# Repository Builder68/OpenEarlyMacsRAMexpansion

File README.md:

# Open Early Macs RAM Expansion
#
 ## SUMMARY

This upgrade utilizes 1Mb x 16-bit RAM ICs with 1024 refresh cycles, providing up to 4MB of RAM for Macintosh 128K and 512K equipped with the 128KB ROM (Macintosh Plus ROM). 
Testing has confirmed compatibility with a Macintosh 512Ke, including concurrent use with the ROM-INATOR board. Furthermore, installing this memory expansion alongside a SCSI card (like the MacSnap SCSI) enables the 128KB ROM to identify the machine as a Mac Plus.

*Attention: Due to the way the ROM-INATOR board determines the Mac model it's installed on (Mac Plus or Mac 512Ke), its ROM image needs to be [patched](https://68kmla.org/bb/index.php?threads/early-macintosh-home-brew-4mb-memory-upgrade-board-development.47308/post-544271) before installing this RAM expansion board or any other RAM upgrade.*

## PROJECT STATUS

This project is fully functional on a Mac 512Ke. Although it's expected to work on Mac 128K or 512K systems with the 128KB ROM, this specific compatibility hasn't been tested yet.

## KEY FEATURES

* One single detachable RAM board, which taps several signals through bodge wires with JST connectors and either piggyback sockets or pin headers soldered to components on the LB.
* You can disable RAM expansion through DIP switches on the board.
* A solder jumper allows you to select between two memory size configurations: 2MB or 4MB.
* Compatible with FPM or EDO CMOS RAM ICs of 1Mb x 16 bits.
* The PCB dimensions are designed to allow concurrent installation with [Demik's MacSnap SCSI replica board](https://github.com/demik/MacSnap-SCSI//). 
* No extensions or additional software are needed; Mac will automatically recognize all the configured RAM upon startup.
## ASSEMBLY

While the assembly process is straightforward, it can be challenging. Reflow soldering, or using solder paste and a heat gun, is highly recommended for the RAM chips and most SMD components. 

Although this might sound highly obvious, I must say it:

Please be sure to get the right schematics for your LB revision.

## SPECIAL THANKS

This project wouldn't be where it is today without the significant contributions of Golden Potato. His collaboration on developing and testing this design was instrumental. From the beginning, his desire was that this design should be free and open source with both of our names attached to it. 
#
#

### 1. RAM EXPANSION BOARD 
Front

Back

## 2. BOM

#
## 3. BEFORE INSTALLING 

### 3.1 Socket machine headers at RP2 & RP3 

Prior to installing the expansion board, resistor arrays RP2 and RP3 must be removed from the LB and replaced with socket pin machine headers.
#
## 4. INSTALLATION

### 4.1 Pin headers
  
Solder machine pin headers (male to male) onto ICs U12E, U13E, and U4F. Then, the board connects to these pin headers via sockets soldered on the backside of the expansion board.

Optionally, you can instead solder DIP sockets onto U12E, U13E, and U4F (piggybacked) and solder male-to-male pin headers to the expansion board.

## 5. Signals to JST connectors

The following tables shows the signals that are collected via bodged wires from the LB to the JST connectors J11 and J12:

### 5.1 J11

| SIGNAL          | Location       | Pin N° | Comment         |
|:---------------:|:--------------:|:------------:|:---------------:|
| /SNDPG2         |Pin N°5 - U2F   |1             |                 |
| /DMA            |Pin N°15 - U2F  |2             |                 |
| VA6             |Pin N°6 - U2F   |3             |                 |
| VA13            |Pin N°12 - U3G  |4             |                 |
| A18             |Pin N°46 - CPU  |5             |                 |
| VA5             |Pin N°13 - U3G  |6             |                 |

### 5.2 J12

| SIGNAL                | Location on LB   | Pin N° | Comment         |
|:---------------------:|:----------------:|:------------:|:---------------:|
| A17                   |Pin N°45 - CPU    |1             |                 |
| A20                   |Pin N°5 - U4D     |2             |                 |
| A19                   |Pin N°3 - U3D     |3             |                 |
| A21                   |Pin N°50 - CPU    |4             |                 |
| /RAS                  |Left Leg of R4 or Pin N°14 - 4D   |5             |                 | 
| R/WF                  |Right Leg of R33  |6             |                 |
#

## 6. SETTINGS

### 6.1 RAM Expansion Board

#### 6.1.1 IC RAM Type (FPM / EDO)

Solder jumpers JP1 & JP2 selects between FPM or EDO RAM IC types

#### 6.1.2 RAM Size

|JP3              |RAM Size           |
|:---------------:|:-----------------:|
| 2-3             | 2MB               |
| 1-2.            | 4MB.              |

#### 6.1.3 RAM Expansion Enabling (SWB1 & SWB2)

SWB1
|S n°|Expansion RAM Enabled  |  Expansion RAM Disabled |
|:--:|:------------------:|:-------------------:|
| 1  | ON                 |               OFF   |
| 2  | OFF                |               ON    |
| 3  | ON                 |               OFF   |
| 4  | OFF                |               ON    |
| 5  | ON                 |               OFF   |
| 6  | OFF                |               ON    |

SWB2
|S n°|Expansion RAM Enabled  |  Expansion RAM Disabled |
|:--:|:------------------:|:-------------------:|
| 1  | ON                 |               OFF   |
| 2  | OFF                |               ON    |
| 3  | ON                 |               OFF   |
| 4  | OFF                |               ON    |
| 5  | ON                 |               OFF   |
| 6  | ON                 |               OFF   |
| 7  | OFF                |               ON    |
| 8  | OFF                |               ON    |

*Attention: double check all connections and DIP switch settings before power-up*

Good luck. Let us know how it goes here: https://68kmla.org/bb/index.php?threads/early-macintosh-home-brew-4mb-memory-upgrade-board-development.47308/

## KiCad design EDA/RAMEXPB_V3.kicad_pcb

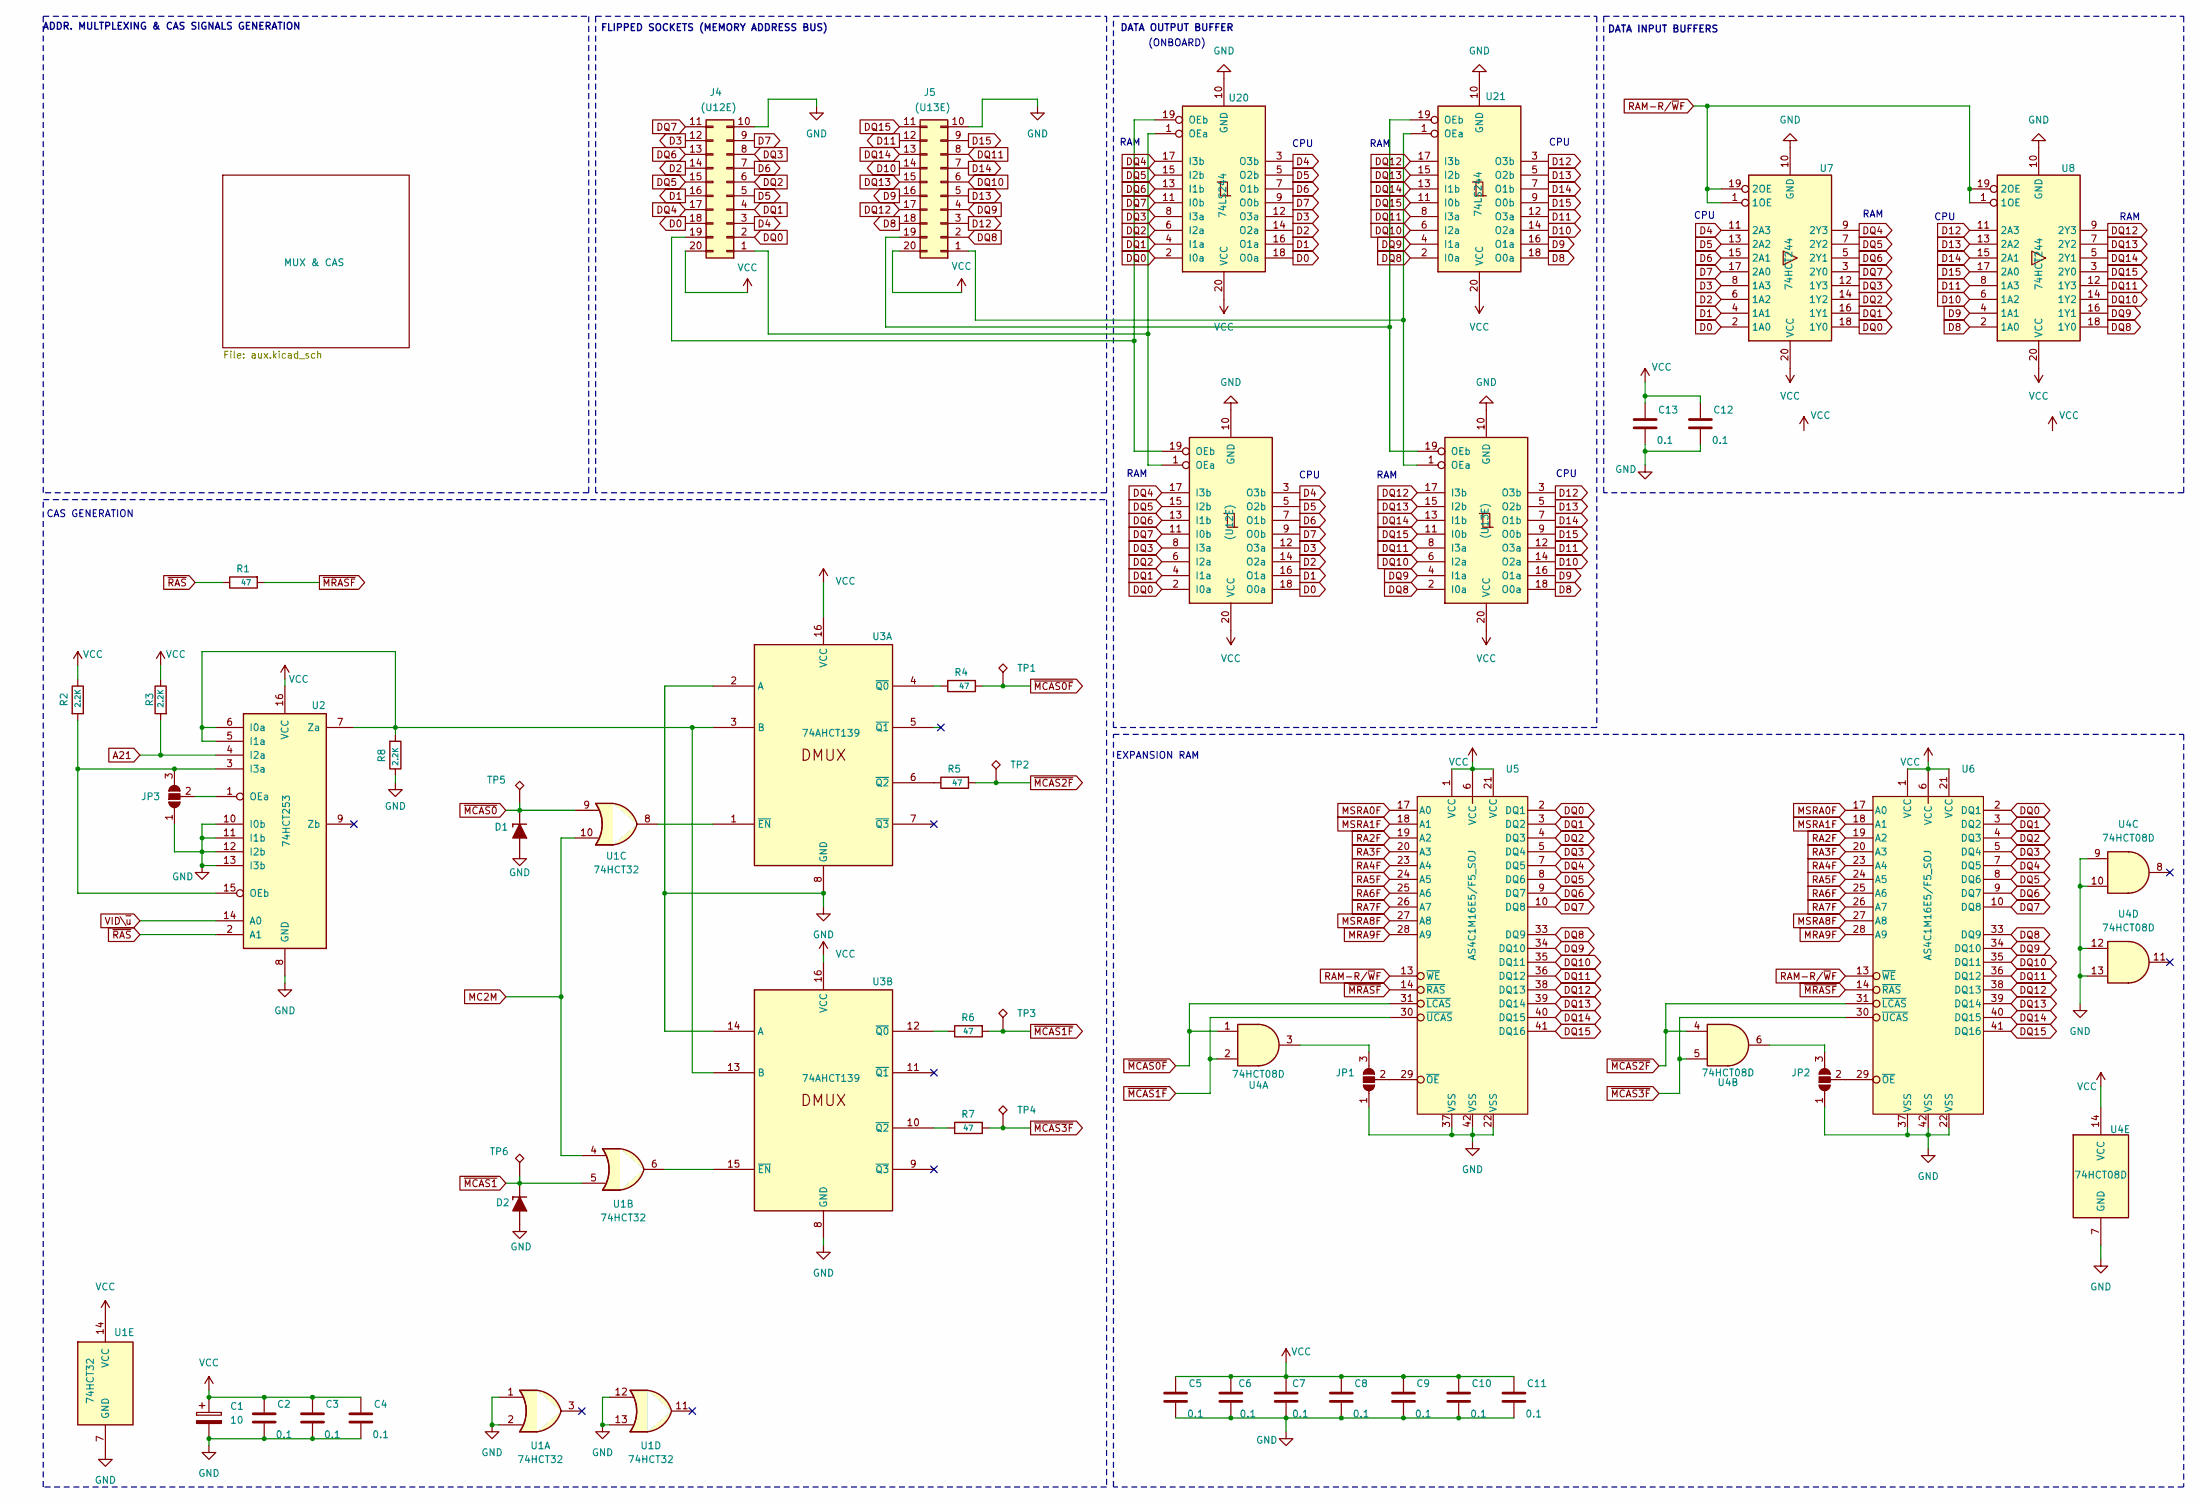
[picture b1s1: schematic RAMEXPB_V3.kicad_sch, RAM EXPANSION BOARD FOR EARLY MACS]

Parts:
C1: 10; CP_EIA-6032-28_Kemet-C_Pad2.25x2.35mm_HandSolder
C2, C3, C4, C5, C6, C7, C8, C9, C10, C11, C12, C13: 0.1; C_0805_2012Metric_Pad1.18x1.45mm_HandSolder
D1, D2: SZMMSZ5V1T1G; D_SOD-123
J4: (U12E); DIP-20_Socket_INV_Flip
J5: (U13E); DIP-20_Socket_INV_Flip
JP1, JP2, JP3: SolderJumper_3_Open; SolderJumper-3_P1.3mm_Open_RoundedPad1.0x1.5mm_NumberLabels
R1, R4, R5, R6, R7: 47; R_0805_2012Metric_Pad1.20x1.40mm_HandSolder
R2, R3, R8: 2.2K; R_0805_2012Metric_Pad1.20x1.40mm_HandSolder
TP1, TP2, TP3, TP4, TP5, TP6: TestPoint_Alt; TestPoint_Pad_D1.0mm
U1: 74HCT32; SO-14_3.9x8.65mm_P1.27mm
U2: 74HCT253; SO-16_3.9x9.9mm_P1.27mm
U3: 74AHCT139; SO-16_3.9x9.9mm_P1.27mm
U4: 74HCT08D; SO-14_3.9x8.65mm_P1.27mm
U5, U6: AS4C1M16E5/F5_SOJ; SOJ-42_400mil
U7, U8: 74HCT244; SOIC-20W_7.5x12.8mm_P1.27mm
U12: (U12E); DIP-20_W7.62mm_Socket
U13: (U13E); DIP-20_W7.62mm_Socket
U20, U21: 74LS244; Socket_DIP-20_7.62mm_Conn_Hole1mm_custom

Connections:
A21: R3.2, U2.4 (I2a); also elsewhere on the board
D0: J4.18, U7.2 (1A0), U12.18 (O0a), U20.18 (O0a)
D1: J4.16, U7.4 (1A1), U12.16 (O1a), U20.16 (O1a)
D2: J4.14, U7.6 (1A2), U12.14 (O2a), U20.14 (O2a)
D3: J4.12, U7.8 (1A3), U12.12 (O3a), U20.12 (O3a)
D4: J4.3, U7.11 (2A3), U12.3 (O3b), U20.3 (O3b)
D5: J4.5, U7.13 (2A2), U12.5 (O2b), U20.5 (O2b)
D6: J4.7, U7.15 (2A1), U12.7 (O1b), U20.7 (O1b)
D7: J4.9, U7.17 (2A0), U12.9 (O0b), U20.9 (O0b)
D8: J5.18, U8.2 (1A0), U13.18 (O0a), U21.18 (O0a)
D9: J5.16, U8.4 (1A1), U13.16 (O1a), U21.16 (O1a)
D10: J5.14, U8.6 (1A2), U13.14 (O2a), U21.14 (O2a)
D11: J5.12, U8.8 (1A3), U13.12 (O3a), U21.12 (O3a)
D12: J5.3, U8.11 (2A3), U13.3 (O3b), U21.3 (O3b)
D13: J5.5, U8.13 (2A2), U13.5 (O2b), U21.5 (O2b)
D14: J5.7, U8.15 (2A1), U13.7 (O1b), U21.7 (O1b)
D15: J5.9, U8.17 (2A0), U13.9 (O0b), U21.9 (O0b)
DQ0: J4.2, U5.2 (DQ1), U6.2 (DQ1), U7.18 (1Y0), U12.2 (I0a), U20.2 (I0a)
DQ1: J4.4, U5.3 (DQ2), U6.3 (DQ2), U7.16 (1Y1), U12.4 (I1a), U20.4 (I1a)
DQ2: J4.6, U5.4 (DQ3), U6.4 (DQ3), U7.14 (1Y2), U12.6 (I2a), U20.6 (I2a)
DQ3: J4.8, U5.5 (DQ4), U6.5 (DQ4), U7.12 (1Y3), U12.8 (I3a), U20.8 (I3a)
DQ4: J4.17, U5.7 (DQ5), U6.7 (DQ5), U7.9 (2Y3), U12.17 (I3b), U20.17 (I3b)
DQ5: J4.15, U5.8 (DQ6), U6.8 (DQ6), U7.7 (2Y2), U12.15 (I2b), U20.15 (I2b)
DQ6: J4.13, U5.9 (DQ7), U6.9 (DQ7), U7.5 (2Y1), U12.13 (I1b), U20.13 (I1b)
DQ7: J4.11, U5.10 (DQ8), U6.10 (DQ8), U7.3 (2Y0), U12.11 (I0b), U20.11 (I0b)
DQ8: J5.2, U5.33 (DQ9), U6.33 (DQ9), U8.18 (1Y0), U13.2 (I0a), U21.2 (I0a)
DQ9: J5.4, U5.34 (DQ10), U6.34 (DQ10), U8.16 (1Y1), U13.4 (I1a), U21.4 (I1a)
DQ10: J5.6, U5.35 (DQ11), U6.35 (DQ11), U8.14 (1Y2), U13.6 (I2a), U21.6 (I2a)
DQ11: J5.8, U5.36 (DQ12), U6.36 (DQ12), U8.12 (1Y3), U13.8 (I3a), U21.8 (I3a)
DQ12: J5.17, U5.38 (DQ13), U6.38 (DQ13), U8.9 (2Y3), U13.17 (I3b), U21.17 (I3b)
DQ13: J5.15, U5.39 (DQ14), U6.39 (DQ14), U8.7 (2Y2), U13.15 (I2b), U21.15 (I2b)
DQ14: J5.13, U5.40 (DQ15), U6.40 (DQ15), U8.5 (2Y1), U13.13 (I1b), U21.13 (I1b)
DQ15: J5.11, U5.41 (DQ16), U6.41 (DQ16), U8.3 (2Y0), U13.11 (I0b), U21.11 (I0b)
GND: C1.2, C2.2, C3.2, C4.2, C5.2, C6.2, C7.2, C8.2, C9.2, C10.2, C11.2, C12.2, C13.2, D1.2 (A), D2.2 (A), J4.10, J5.10, JP1.1 (A), JP2.1 (A), JP3.1 (A), R8.1, U1.1, U1.2, U1.7 (GND), U1.12, U1.13, U2.8 (GND), U2.10 (I0b), U2.11 (I1b), U2.12 (I2b), U2.13 (I3b), U3.2 (A), U3.8 (GND), U3.14 (A), U4.7 (GND), U4.9, U4.10, U4.12, U4.13, U5.22 (VSS), U5.37 (VSS), U5.42 (VSS), U6.22 (VSS), U6.37 (VSS), U6.42 (VSS), U7.10 (GND), U8.10 (GND), U12.10 (GND), U13.10 (GND), U20.10 (GND), U21.10 (GND); also elsewhere on the board
MC2M: U1.4, U1.10; also elsewhere on the board
MRA9F: U5.28 (A9), U6.28 (A9); also elsewhere on the board
MSRA0F: U5.17 (A0), U6.17 (A0); also elsewhere on the board
MSRA1F: U5.18 (A1), U6.18 (A1); also elsewhere on the board
MSRA8F: U5.27 (A8), U6.27 (A8); also elsewhere on the board
unnamed: J4.1, U12.1 (OEa), U20.1 (OEa)
unnamed: J4.19, U12.19 (OEb), U20.19 (OEb)
unnamed: J5.1, U13.1 (OEa), U21.1 (OEa)
unnamed: J5.19, U13.19 (OEb), U21.19 (OEb)
unnamed: JP1.3 (B), U4.3
unnamed: JP1.2 (C), U5.29 (~OE)
unnamed: JP2.3 (B), U4.6
unnamed: JP2.2 (C), U6.29 (~OE)
unnamed: JP3.3 (B), R2.2, U2.3 (I3a), U2.15 (OEb)
unnamed: JP3.2 (C), U2.1 (OEa)
unnamed: R8.2, U2.5 (I1a), U2.6 (I0a), U2.7 (Za), U3.3 (B), U3.13 (B)
unnamed: U1.8, U3.1 (~EN)
unnamed: R4.1, U3.4 (~Q0)
unnamed: R5.1, U3.6 (~Q2)
unnamed: U1.6, U3.15 (~EN)
unnamed: R6.1, U3.12 (~Q0)
unnamed: R7.1, U3.10 (~Q2)
RA2F: U5.19 (A2), U6.19 (A2); also elsewhere on the board
RA3F: U5.20 (A3), U6.20 (A3); also elsewhere on the board
RA4F: U5.23 (A4), U6.23 (A4); also elsewhere on the board
RA5F: U5.24 (A5), U6.24 (A5); also elsewhere on the board
RA6F: U5.25 (A6), U6.25 (A6); also elsewhere on the board
RA7F: U5.26 (A7), U6.26 (A7); also elsewhere on the board
RAM-R/~WF: U5.13 (~WE), U6.13 (~WE), U7.1 (1OE), U7.19 (2OE), U8.1 (1OE), U8.19 (2OE); also elsewhere on the board
VCC: C1.1, C2.1, C3.1, C4.1, C5.1, C6.1, C7.1, C8.1, C9.1, C10.1, C11.1, C12.1, C13.1, J4.20, J5.20, R2.1, R3.1, U1.14 (VCC), U2.16 (VCC), U3.16 (VCC), U4.14 (VCC), U5.1 (VCC), U5.6 (VCC), U5.21 (VCC), U6.1 (VCC), U6.6 (VCC), U6.21 (VCC), U7.20 (VCC), U8.20 (VCC), U12.20 (VCC), U13.20 (VCC), U20.20 (VCC), U21.20 (VCC); also elsewhere on the board
VID\~u: U2.14 (A0); also elsewhere on the board
~MCAS0F: R4.2, TP1.1, U4.1, U5.31 (~LCAS)
~MCAS0: D1.1 (K), TP5.1, U1.9; also elsewhere on the board
~MCAS1F: R6.2, TP3.1, U4.2, U5.30 (~UCAS)
~MCAS1: D2.1 (K), TP6.1, U1.5; also elsewhere on the board
~MCAS2F: R5.2, TP2.1, U4.4, U6.31 (~LCAS)
~MCAS3F: R7.2, TP4.1, U4.5, U6.30 (~UCAS)
~MRASF: R1.2, U5.14 (~RAS), U6.14 (~RAS)
~RAS: R1.1, U2.2 (A1); also elsewhere on the board

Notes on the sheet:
RAM
CPU
DATA INPUT BUFFERS
EXPANSION RAM
DATA OUTPUT BUFFER
CAS GENERATION
FLIPPED SOCKETS (MEMORY ADDRESS BUS)
(ONBOARD)
ADDR. MULTPLEXING & CAS SIGNALS GENERATION

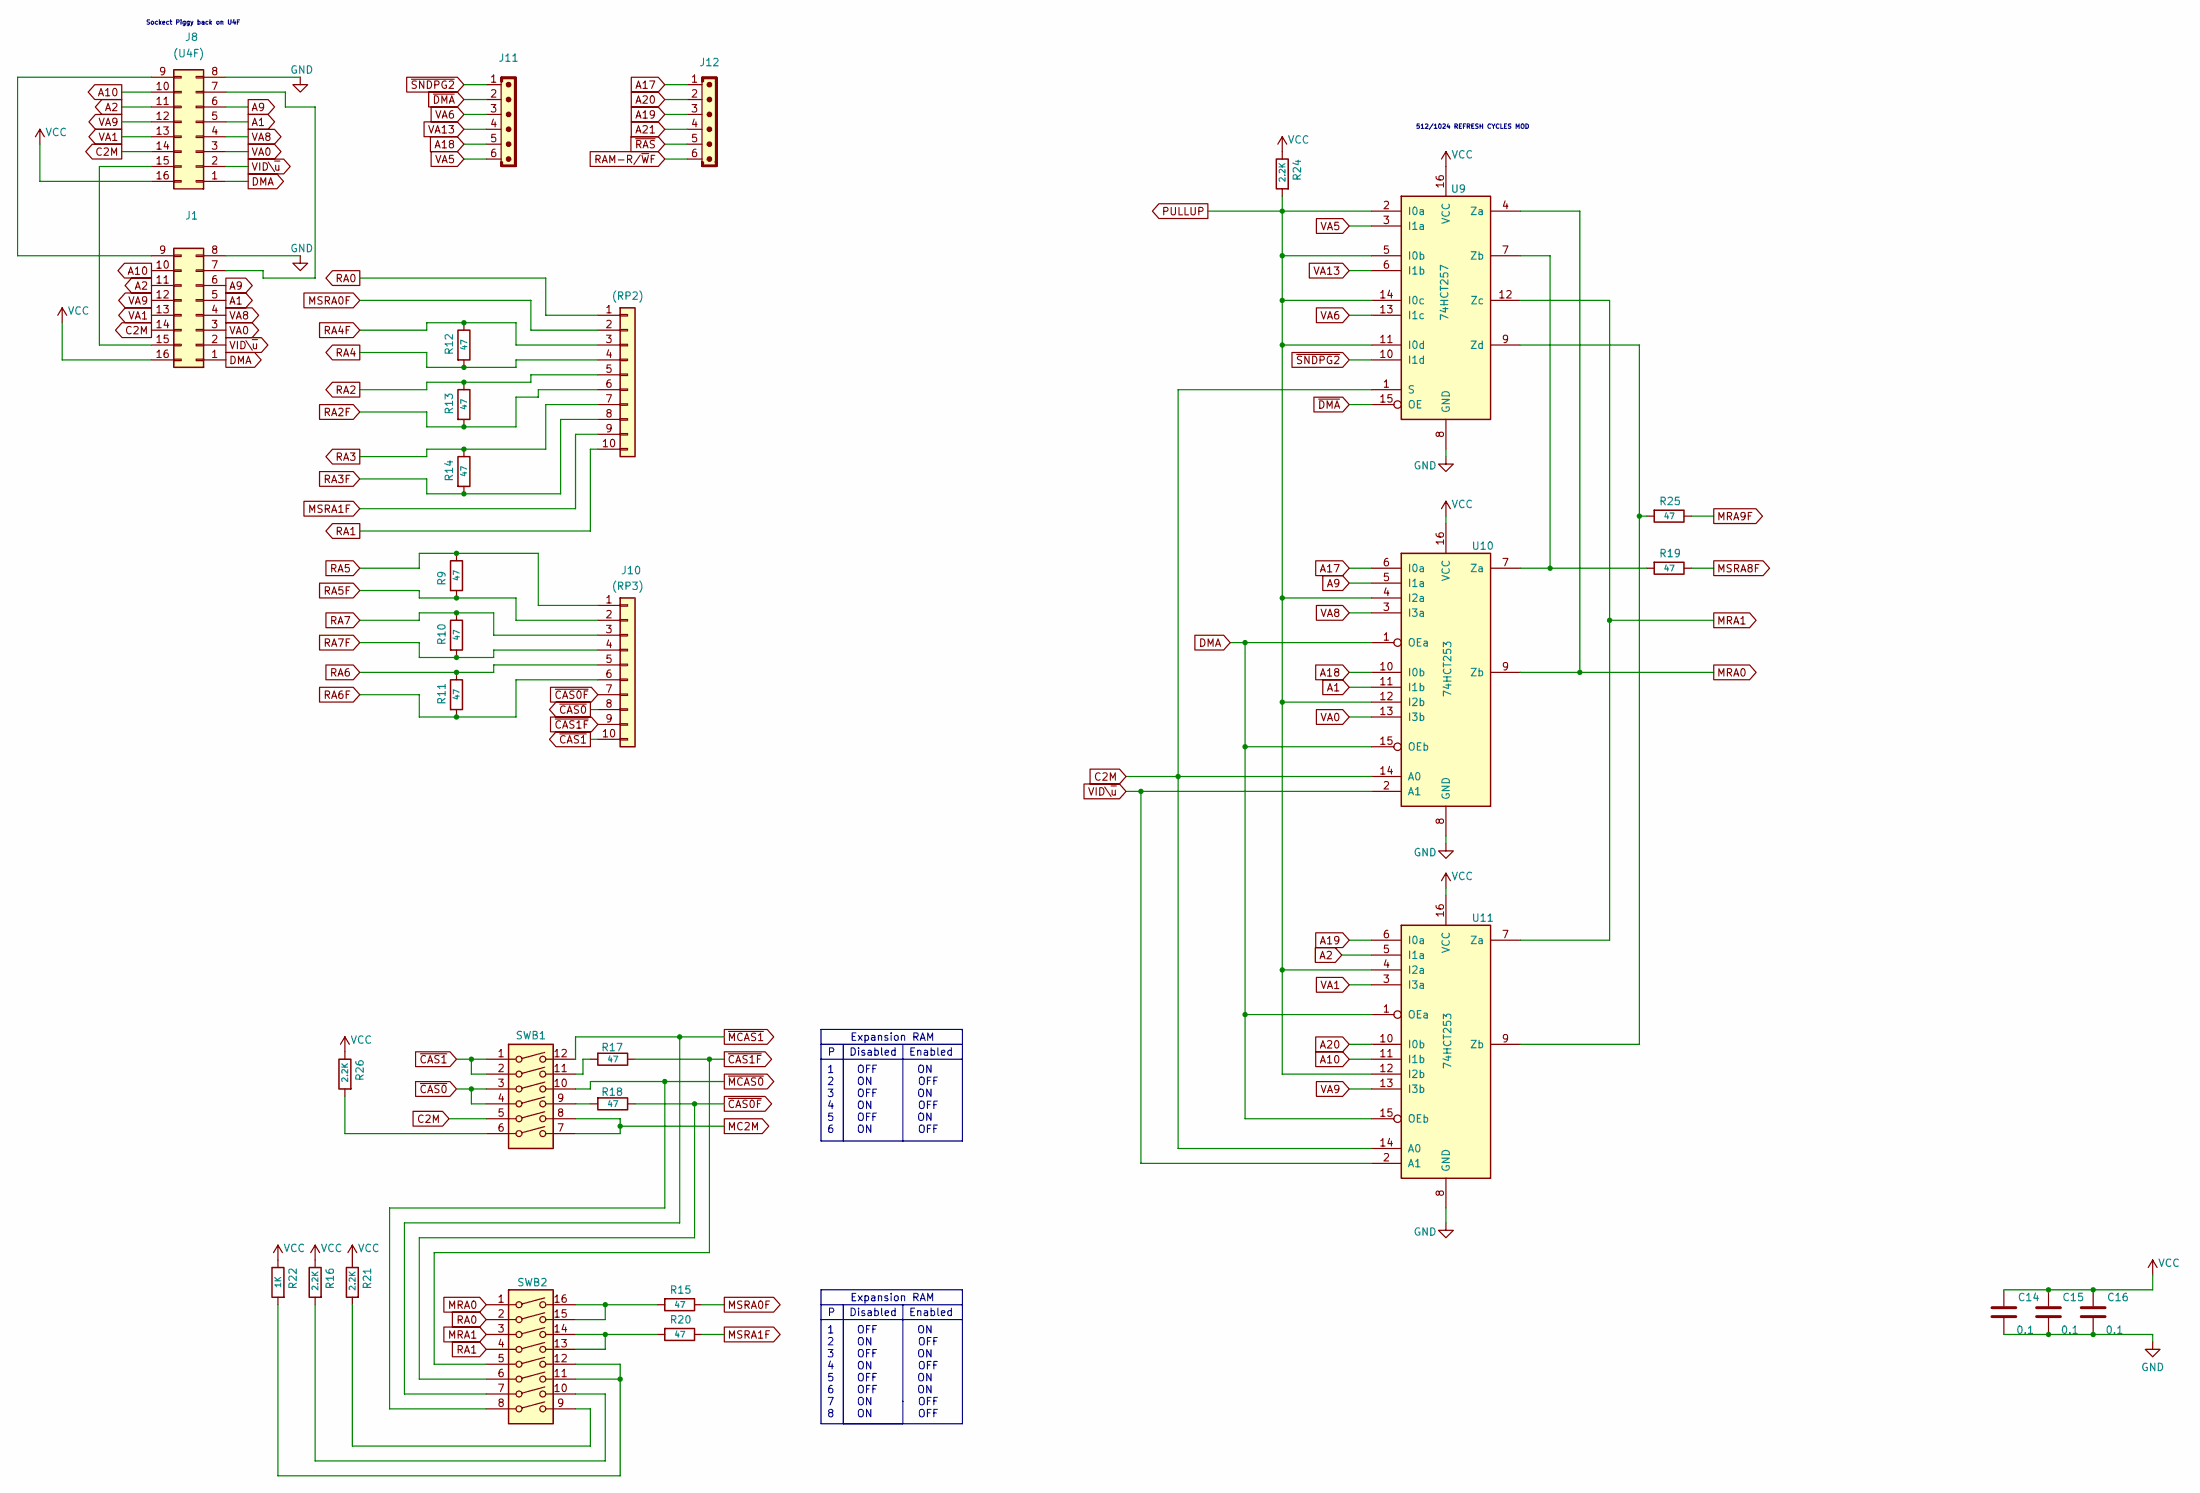
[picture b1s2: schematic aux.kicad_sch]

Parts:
C14, C15, C16: 0.1; C_0805_2012Metric_Pad1.18x1.45mm_HandSolder
J1: (U4F); DIP-16_W7.62mm_Socket
J8: (U4F); DIP-16_INVERTED_FLIP
J9: (RP2); PinHeader_1x10_P2.54mm_Vertical
J10: (RP3); PinHeader_1x10_P2.54mm_Vertical
J11, J12: JST_06; JST_PH_S6B-PH-K_1x06_P2.00mm_Horizontal
R9, R10, R11, R12, R13, R14, R15, R17, R18, R19, R20, R25: 47; R_0805_2012Metric_Pad1.20x1.40mm_HandSolder
R16, R21, R24, R26: 2.2K; R_0805_2012Metric_Pad1.20x1.40mm_HandSolder
R22: 1K; R_0805_2012Metric_Pad1.20x1.40mm_HandSolder
SWB1: SW_DIP_x06; SW_DIP_SPSTx06_Slide_Omron_A6H-6101_W6.15mm_P1.27mm
SWB2: SW_DIP_x08; SW_DIP_SPSTx08_Slide_Omron_A6H-8101_W6.15mm_P1.27mm
U9: 74HCT257; SO-16_3.9x9.9mm_P1.27mm
U10, U11: 74HCT253; SO-16_3.9x9.9mm_P1.27mm

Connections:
A1: J1.5, J8.5, U10.11 (I1b)
A2: J1.11, J8.11, U11.5 (I1a)
A9: J1.6, J8.6, U10.5 (I1a)
A10: J1.10, J8.10, U11.11 (I1b)
A17: J12.1, U10.6 (I0a)
A18: J11.5, U10.10 (I0b)
A19: J12.3, U11.6 (I0a)
A20: J12.2, U11.10 (I0b)
A21: J12.4; also elsewhere on the board
C2M: J1.14, J8.14, SWB1.5, U9.1 (S), U10.14 (A0), U11.14 (A0)
DMA: J1.1, J8.1, U10.1 (OEa), U10.15 (OEb), U11.1 (OEa), U11.15 (OEb)
GND: C14.2, C15.2, C16.2, J1.8, J8.8, U9.8 (GND), U10.8 (GND), U11.8 (GND); also elsewhere on the board
MC2M: SWB1.7, SWB1.8; also elsewhere on the board
MRA0: SWB2.1, U9.4 (Za), U10.9 (Zb)
MRA1: SWB2.3, U9.12 (Zc), U11.7 (Za)
MRA9F: R25.1; also elsewhere on the board
MSRA0F: J9.2, R15.1; also elsewhere on the board
MSRA1F: J9.9, R20.1; also elsewhere on the board
MSRA8F: R19.1; also elsewhere on the board
unnamed: J1.7, J8.7
unnamed: J1.9, J8.9
unnamed: J1.15, J8.15
unnamed: R15.2, SWB2.15, SWB2.16
unnamed: R16.2, SWB2.10
unnamed: R17.2, SWB1.11
unnamed: R18.2, SWB1.9
unnamed: R20.2, SWB2.13, SWB2.14
unnamed: R21.2, SWB2.9
unnamed: R22.2, SWB2.11, SWB2.12
unnamed: R26.2, SWB1.6
unnamed: R19.2, U9.7 (Zb), U10.7 (Za)
unnamed: R25.2, U9.9 (Zd), U11.9 (Zb)
PULLUP: R24.2, U9.2 (I0a), U9.5 (I0b), U9.11 (I0d), U9.14 (I0c), U10.4 (I2a), U10.12 (I2b), U11.4 (I2a), U11.12 (I2b)
RA0: J9.1, SWB2.2
RA1: J9.10, SWB2.4
RA2: J9.5, R13.1
RA2F: J9.6, R13.2; also elsewhere on the board
RA3: J9.7, R14.1
RA3F: J9.8, R14.2; also elsewhere on the board
RA4: J9.4, R12.2
RA4F: J9.3, R12.1; also elsewhere on the board
RA5: J10.1, R9.1
RA5F: J10.2, R9.2; also elsewhere on the board
RA6: J10.5, R11.1
RA6F: J10.6, R11.2; also elsewhere on the board
RA7: J10.3, R10.1
RA7F: J10.4, R10.2; also elsewhere on the board
RAM-R/~WF: J12.6; also elsewhere on the board
VA0: J1.3, J8.3, U10.13 (I3b)
VA1: J1.13, J8.13, U11.3 (I3a)
VA5: J11.6, U9.3 (I1a)
VA6: J11.3, U9.13 (I1c)
VA8: J1.4, J8.4, U10.3 (I3a)
VA9: J1.12, J8.12, U11.13 (I3b)
VA13: J11.4, U9.6 (I1b)
VCC: C14.1, C15.1, C16.1, J1.16, J8.16, R16.1, R21.1, R22.1, R24.1, R26.1, U9.16 (VCC), U10.16 (VCC), U11.16 (VCC); also elsewhere on the board
VID\~u: J1.2, J8.2, U10.2 (A1), U11.2 (A1); also elsewhere on the board
~CAS0F: J10.7, R18.1, SWB2.6
~CAS0: J10.8, SWB1.3, SWB1.4
~CAS1F: J10.9, R17.1, SWB2.5
~CAS1: J10.10, SWB1.1, SWB1.2
~DMA: J11.2, U9.15 (OE)
~MCAS0: SWB1.10, SWB2.8; also elsewhere on the board
~MCAS1: SWB1.12, SWB2.7; also elsewhere on the board
~RAS: J12.5; also elsewhere on the board
~SNDPG2: J11.1, U9.10 (I1d)

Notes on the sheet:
Sockect Piggy back on U4F
Disabled
Enabled
Expansion RAM
512/1024 REFRESH CYCLES MOD
1 OFF ON 2 ON OFF 3 OFF ON 4 ON OFF 5 OFF ON 6 OFF ON 7 ON OFF 8 ON OFF
1 OFF ON 2 ON OFF 3 OFF ON 4 ON OFF 5 OFF ON 6 ON OFF

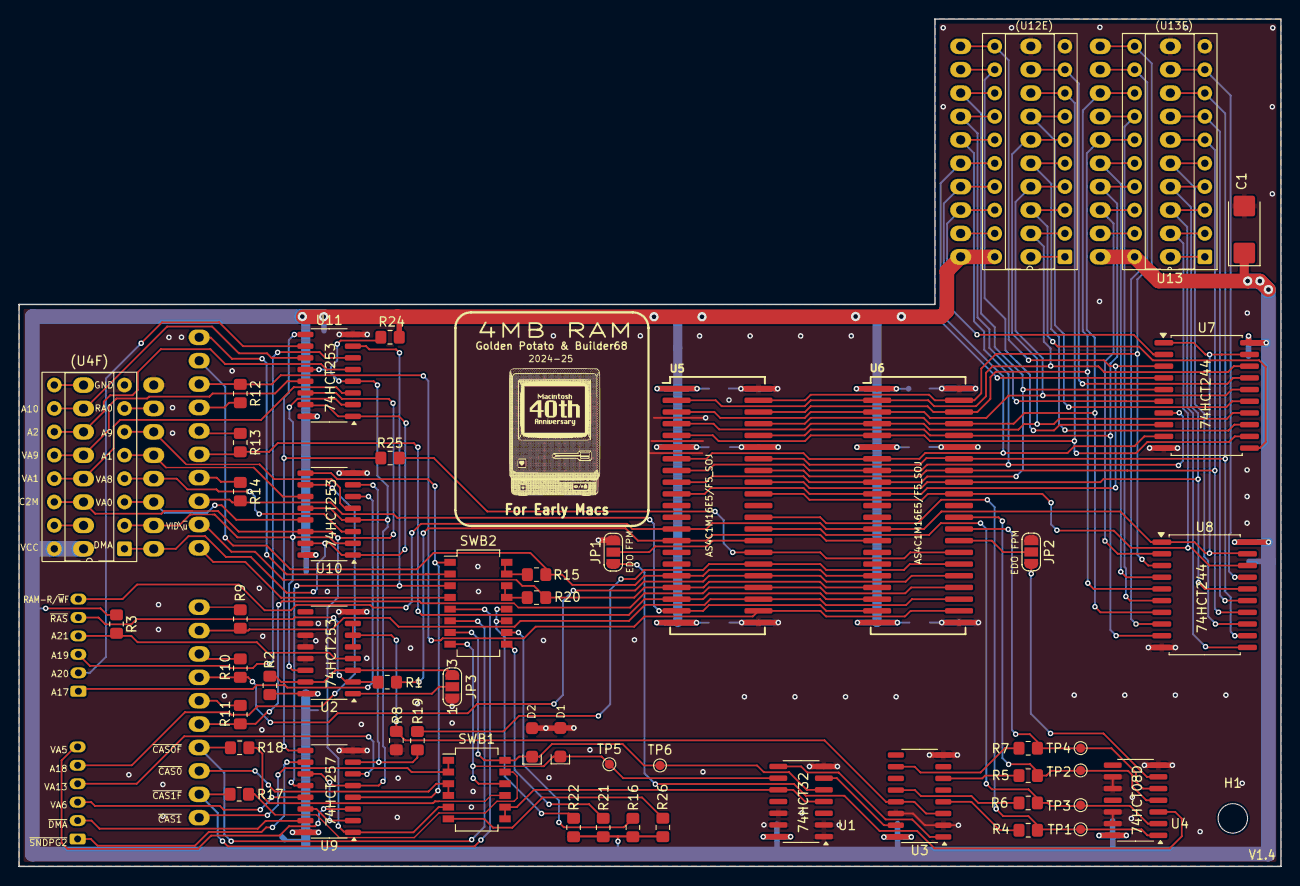
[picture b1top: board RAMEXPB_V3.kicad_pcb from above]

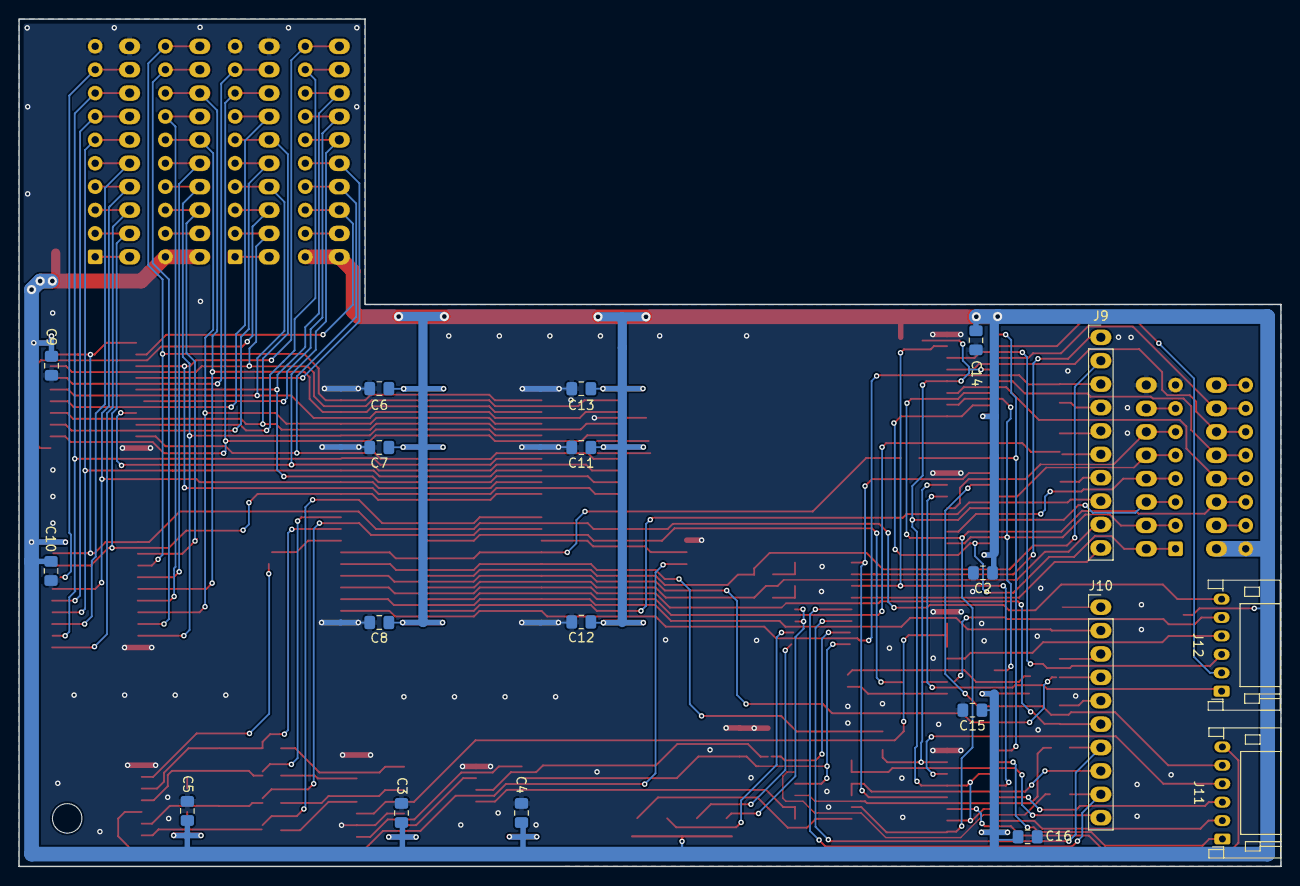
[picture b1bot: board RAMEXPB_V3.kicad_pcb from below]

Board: 2 copper layers, 137.0 x 92.0 mm, 76 parts (22 on the bottom side), 120 nets.

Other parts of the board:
H1: M3_Spacer_H12.7mm; MountingHole_3.2mm_M3_DIN965

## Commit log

2024-11-12 Add files via upload
    Auxiliary Board V2 Gerber Files
2024-11-12 Create LICENSE
2024-11-24 RAM Expansion PCB version 2.1
    Updated PCB design to provide adequate clearance for the integration of a MacSnap SCSI board. No functional changes to the core circuitry.
2024-11-24 Add files via upload
    Interactive HTML BOM
2025-01-09 Add files via upload
    Corrected missing trace to pad #26 on U17 (MSRA8F).
    Fixed legends for SWA1 & RAM settings.
2025-01-10 Add files via upload
    RAM size settings legend corrected
2025-01-10 Several fixes
    - Added missing trace from pad 26 on U17 (MSRA8F). System RAM can now be swapped using DIP switches.
    - Corrected the legends for RAM settings and system RAM swapping.
    - Addressed other minor issues in the tracing of some routes.
2025-04-09 Update LICENSE
2025-04-09 Updated to version 3
2025-04-25 C1 was missing. Fixed!
2025-05-08 74139 outputs fixed
2025-07-03 Update README.md
    IC designations fixed
2025-12-15 PCB V1.4
2025-12-15 Add files via upload
    PCB V1.4
2025-12-15 Update RAM Expansion Board images in README
2025-12-15 Replace old screenshots with updated images
    Updated image references in README.md with new screenshots.
2026-06-11 Fix RAM IC specification in README
    Corrected the RAM IC specification from 2MB to 1Mb.
2026-06-12 Add Ko-fi funding option for builder68
2026-06-12 Fix formatting in FUNDING.yml

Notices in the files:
EDA/RAMEXPB_V3.kicad_pcb:
Licensed under CERN-OHL-S v2
